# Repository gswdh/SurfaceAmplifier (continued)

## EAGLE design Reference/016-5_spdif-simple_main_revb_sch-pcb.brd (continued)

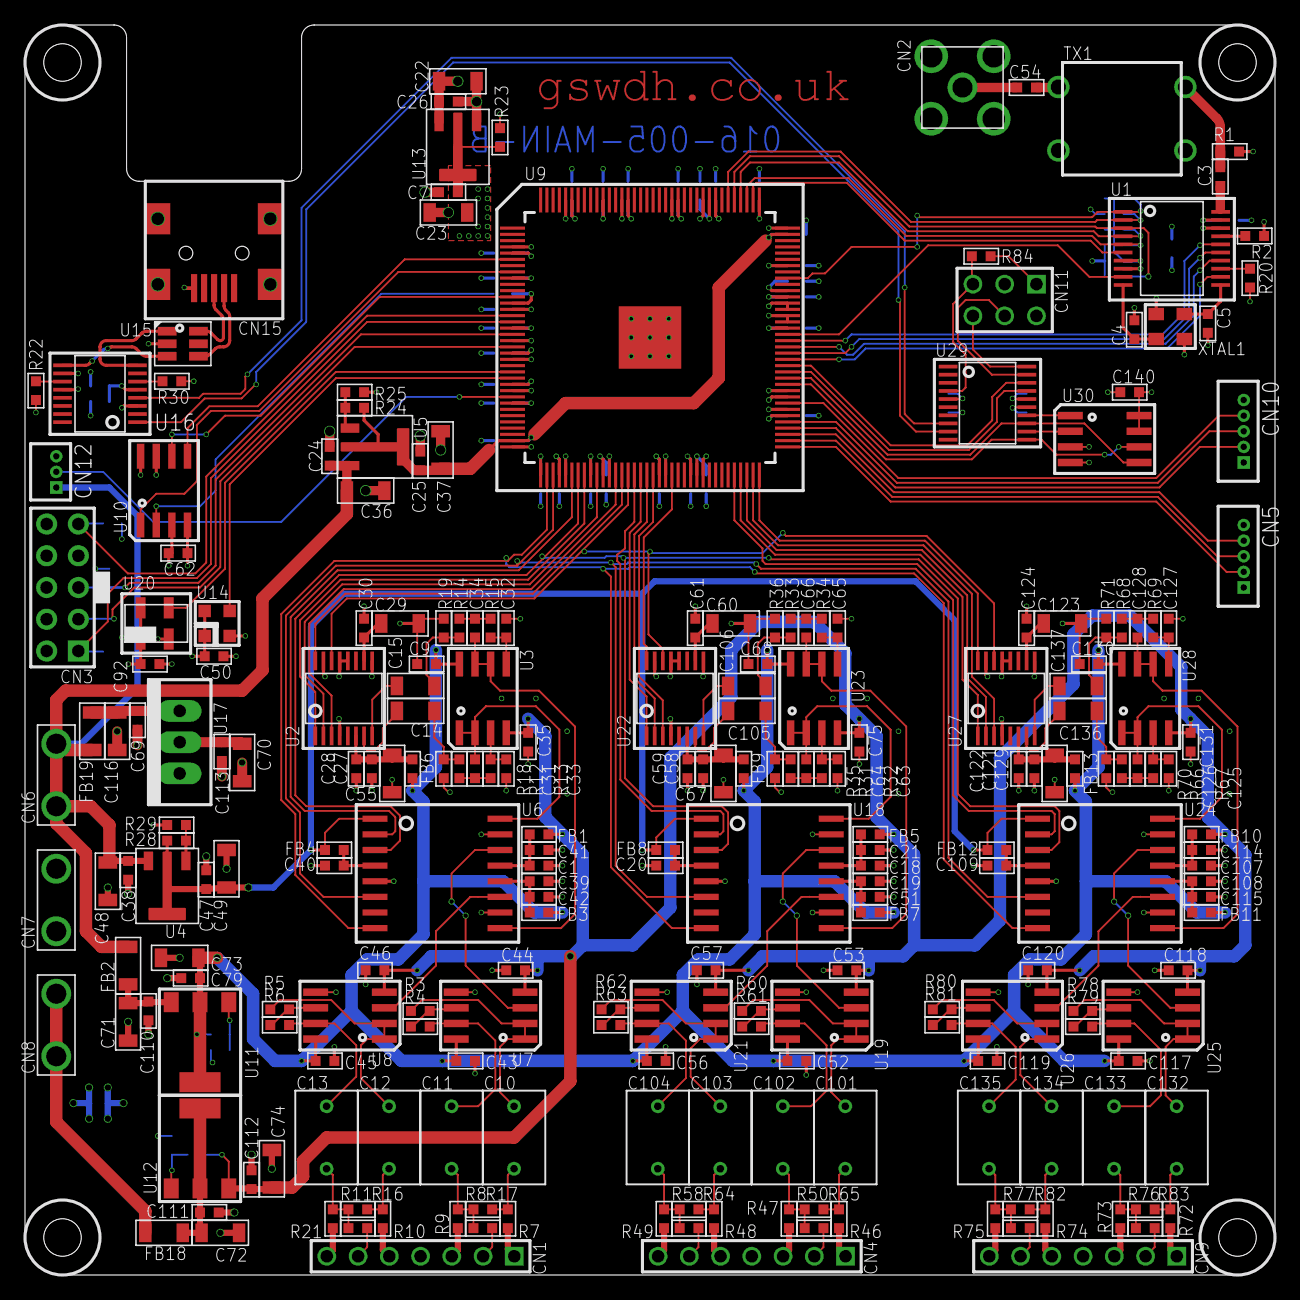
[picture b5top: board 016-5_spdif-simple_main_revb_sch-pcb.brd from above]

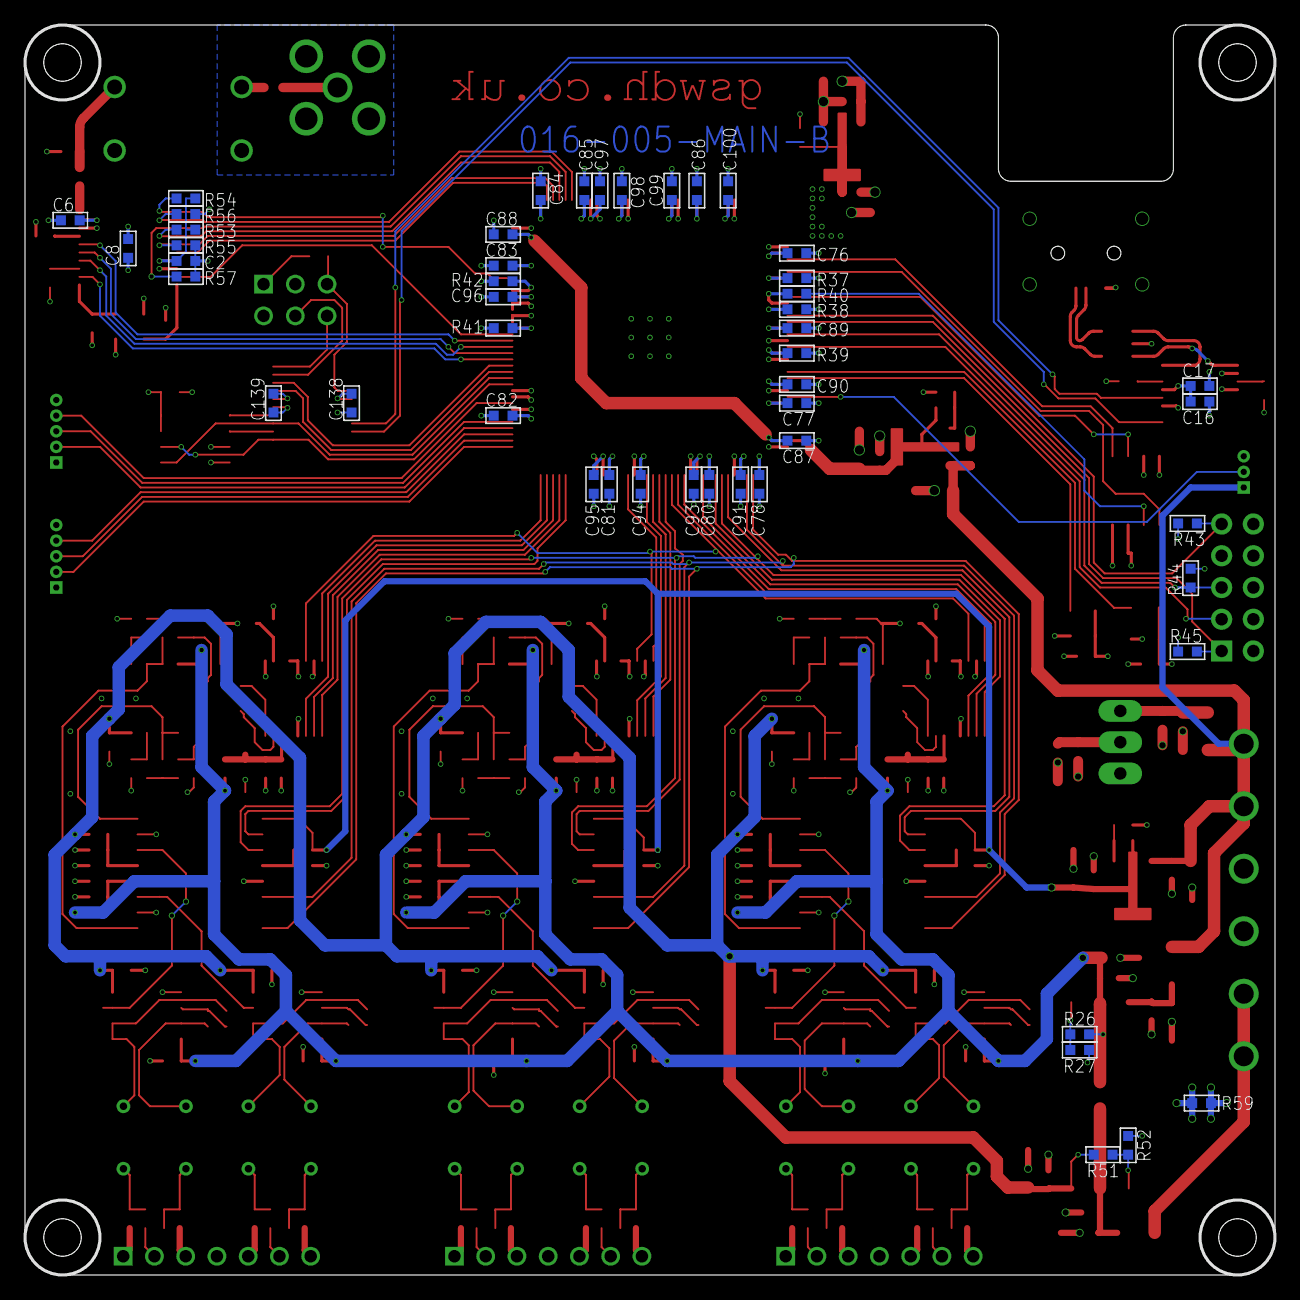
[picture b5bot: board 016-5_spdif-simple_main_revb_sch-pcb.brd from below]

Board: 4 copper layers, 100.0 x 100.0 mm, 289 parts (49 on the bottom side), 189 nets.

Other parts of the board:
U$194: GSWDH.CO.UK

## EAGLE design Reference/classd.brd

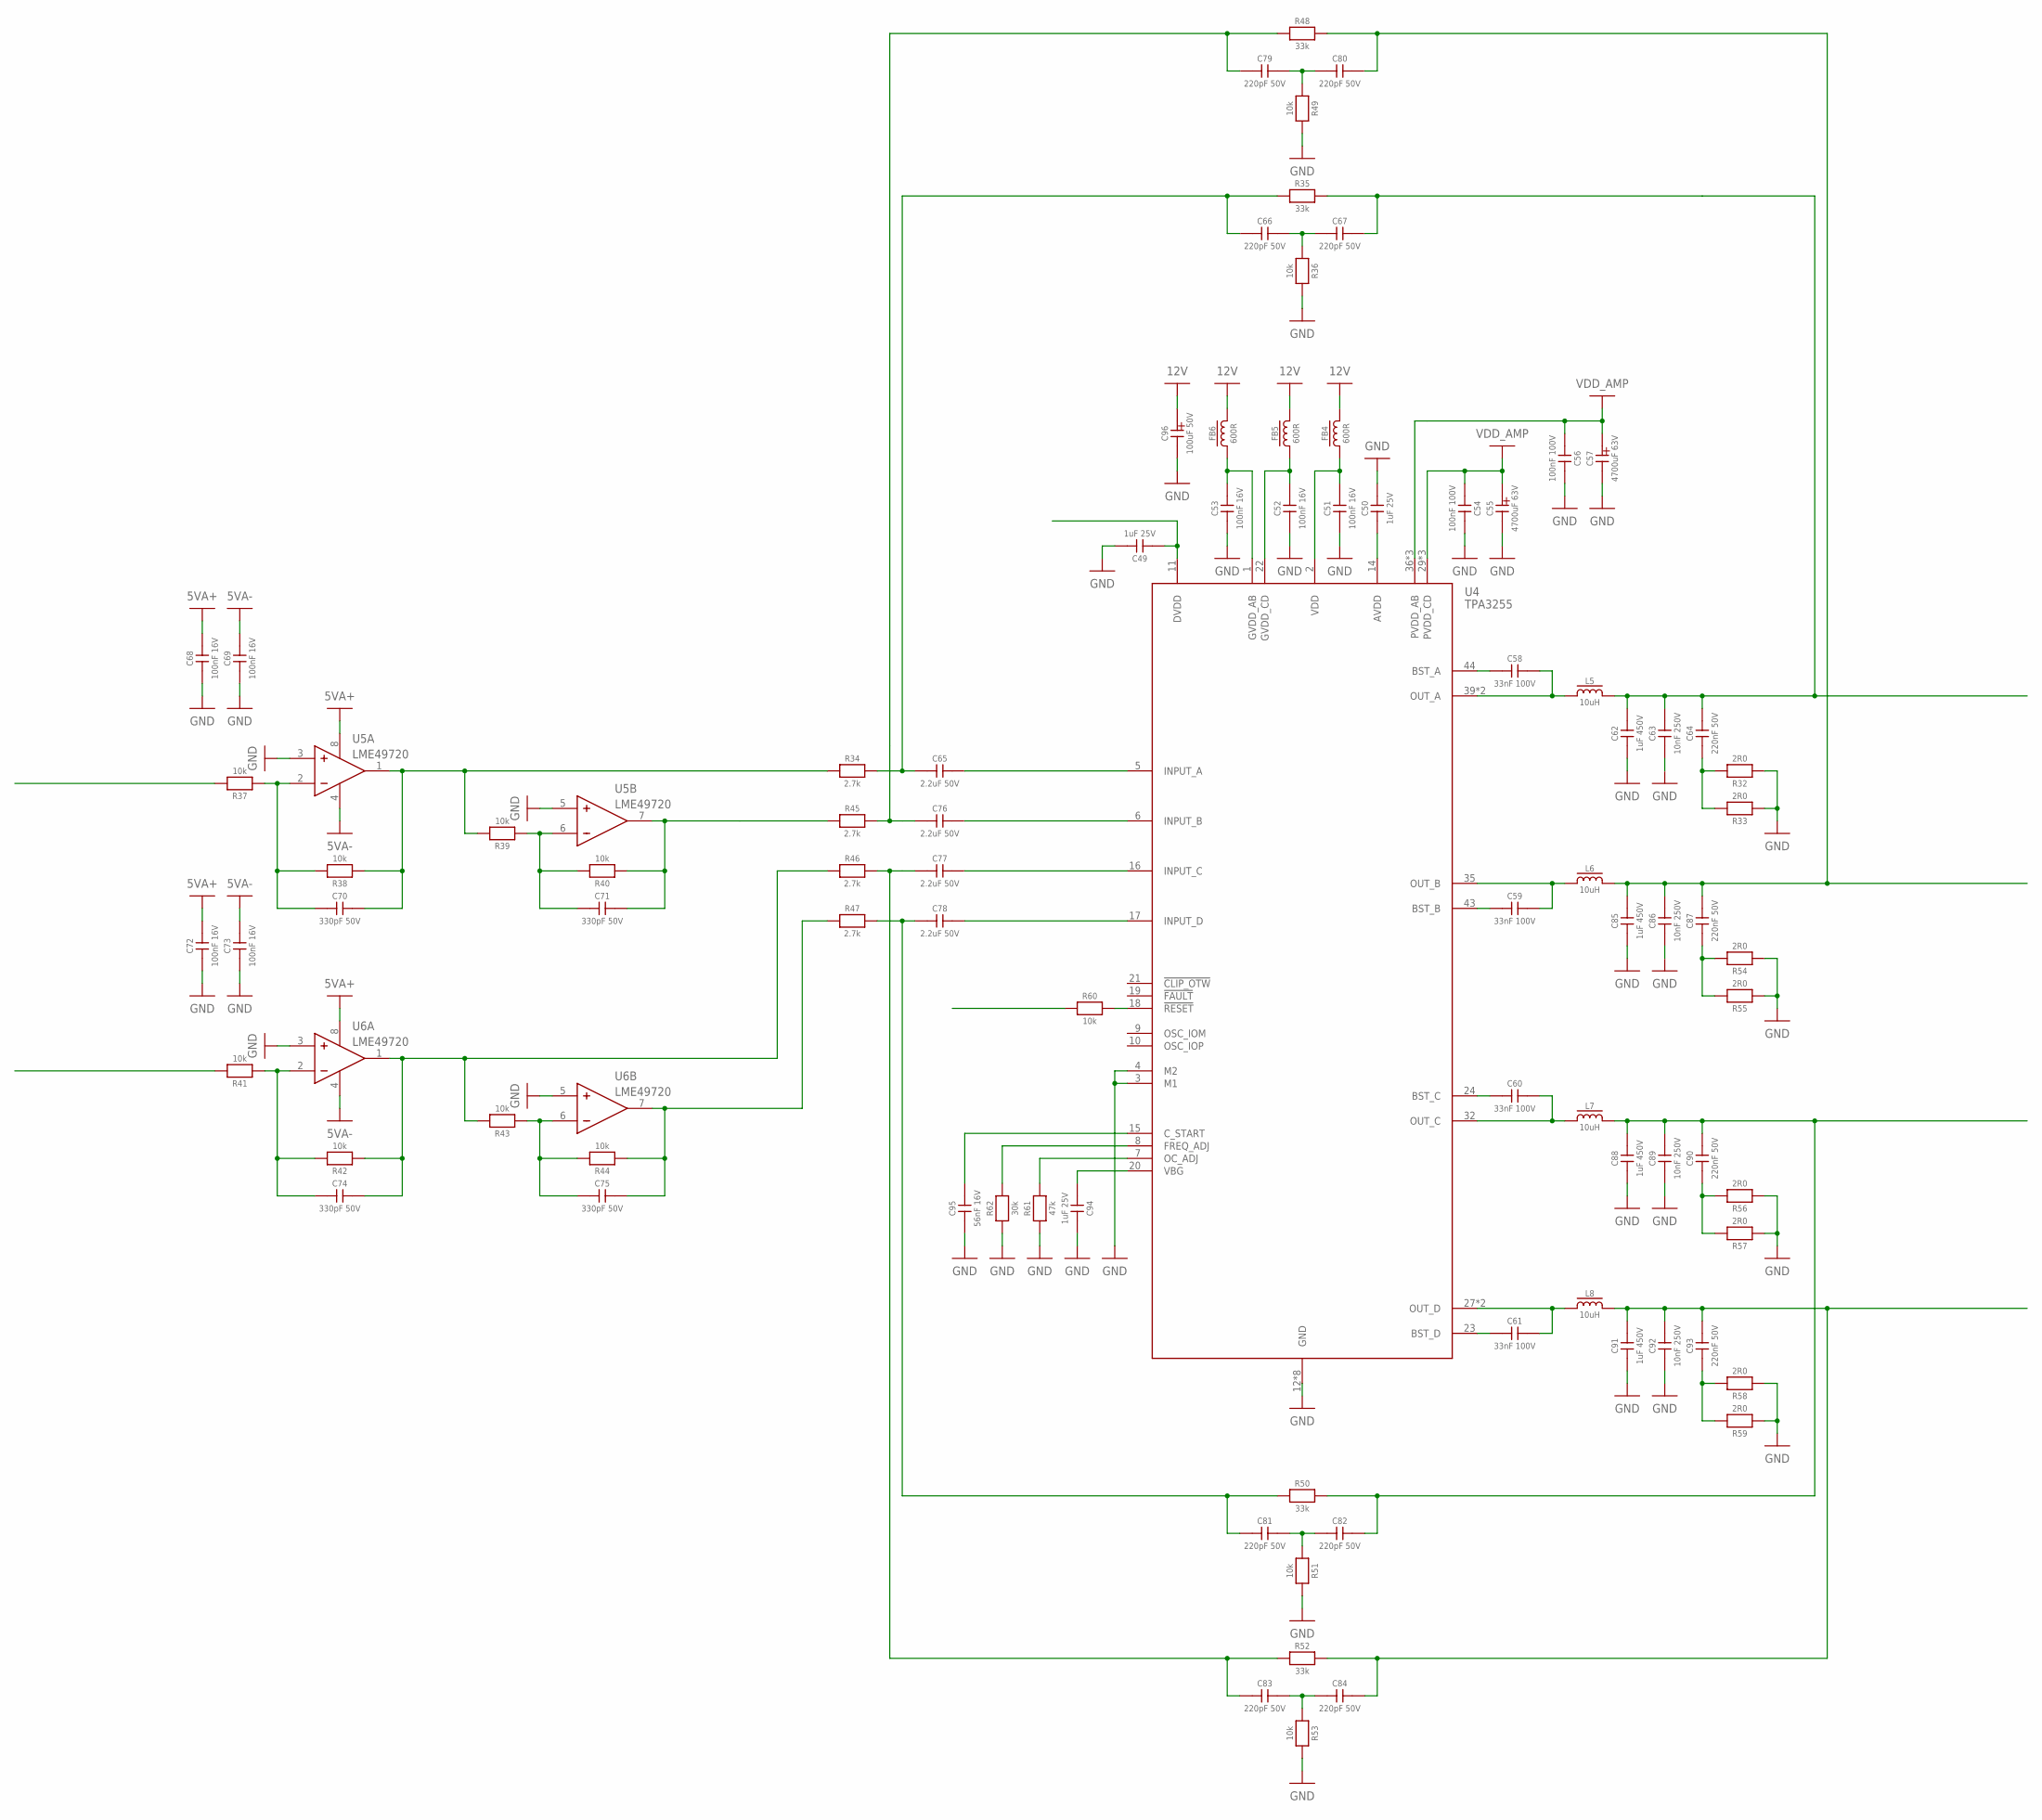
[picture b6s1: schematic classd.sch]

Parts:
C49, C50, C94: 1uF 25V; 0603
C51, C52, C53, C68, C69, C72, C73: 100nF 16V; 0603
C54, C56: 100nF 100V; 0603
C55, C57: 4700uF 63V; 30MM_RADIAL_10MM_PITCH
C58, C59, C60, C61: 33nF 100V; 0603
C62, C85, C88, C91: 1uF 450V; 7X17.5BOX
C63, C86, C89, C92: 10nF 250V; 0603
C64, C87, C90, C93: 220nF 50V; 0603
C65, C76, C77, C78: 2.2uF 50V; 5X7.2BOX
C66, C67, C79, C80, C81, C82, C83, C84: 220pF 50V; 0603
C70, C71, C74, C75: 330pF 50V; 0603
C95: 56nF 16V; 0603
C96: 100uF 50V; 8MM_RADIAL_3.5MM_PITCH
FB4, FB5, FB6: 600R; 0603
L5, L6, L7, L8: 10uH; SRP1265A
R32, R33, R54, R55, R56, R57, R58, R59: 2R0; 1206
R34, R45, R46, R47: 2.7k; 0603
R35, R48, R50, R52: 33k; 0603
R36, R37, R38, R39, R40, R41, R42, R43, R44, R49, R51, R53, R60: 10k; 0603
R61: 47k; 0603
R62: 30k; 0603
U4: TPA3255; HTSSOP44
U5, U6: LME49720; SO8

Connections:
5VA+: C68.2, C72.2, U5.8 (V+), U6.8 (V+)
5VA-: C69.2, C73.2, U5.4 (V-), U6.4 (V-)
12V: C96.P (A), FB4.2, FB5.2, FB6.2
GND: C49.2, C50.2, C51.1, C52.1, C53.1, C54.2, C55.1 (K), C56.2, C57.1 (K), C62.1, C63.1, C68.1, C69.1, C72.1, C73.1, C85.1, C86.1, C88.1, C89.1, C91.1, C92.1, C94.2, C95.1, C96.N (K), R32.1, R33.1, R36.2, R49.2, R51.2, R53.2, R54.1, R55.1, R56.1, R57.1, R58.1, R59.1, R61.1, R62.1, U4.3 (M1), U4.4 (M2), U4.12 (GND), U4.13 (GND), U4.25 (GND), U4.26 (GND), U4.33 (GND), U4.34 (GND), U4.41 (GND), U4.42 (GND), U5.3 (+), U5.5 (+), U6.3 (+), U6.5 (+)
unnamed: C50.1, U4.14 (AVDD)
unnamed: C51.2, FB4.1, U4.2 (VDD)
unnamed: C52.2, FB5.1, U4.22 (GVDD_CD)
unnamed: C53.2, FB6.1, U4.1 (GVDD_AB)
unnamed: C61.1, U4.23 (BST_D)
unnamed: C61.2, L8.1, U4.27 (OUT_D), U4.28 (OUT_D)
unnamed: C60.1, U4.24 (BST_C)
unnamed: C60.2, L7.1, U4.32 (OUT_C)
unnamed: C59.1, U4.43 (BST_B)
unnamed: C59.2, L6.1, U4.35 (OUT_B)
unnamed: C58.1, U4.44 (BST_A)
unnamed: C58.2, L5.1, U4.39 (OUT_A), U4.40 (OUT_A)
unnamed: C64.1, R32.2, R33.2
unnamed: C65.2, U4.5 (INPUT_A)
unnamed: C65.1, C66.1, R34.2, R35.1
unnamed: C62.2, C63.2, C64.2, C67.2, L5.2, R35.2
unnamed: C66.2, C67.1, R36.1
unnamed: C70.2, R34.1, R38.1, R39.2, U5.1 (OUT)
unnamed: C70.1, R37.1, R38.2, U5.2 (-)
unnamed: C71.2, R40.1, R45.1, U5.7 (OUT)
unnamed: C71.1, R39.1, R40.2, U5.6 (-)
unnamed: C74.2, R42.1, R43.2, R46.1, U6.1 (OUT)
unnamed: C74.1, R41.1, R42.2, U6.2 (-)
unnamed: C75.2, R44.1, R47.1, U6.7 (OUT)
unnamed: C75.1, R43.1, R44.2, U6.6 (-)
unnamed: C76.2, U4.6 (INPUT_B)
unnamed: C77.2, U4.16 (INPUT_C)
unnamed: C78.2, U4.17 (INPUT_D)
unnamed: C76.1, C79.1, R45.2, R48.1
unnamed: C80.2, C85.2, C86.2, C87.2, L6.2, R48.2
unnamed: C79.2, C80.1, R49.1
unnamed: C78.1, C81.1, R47.2, R50.1
unnamed: C82.2, C88.2, C89.2, C90.2, L7.2, R50.2
unnamed: C81.2, C82.1, R51.1
unnamed: C77.1, C83.1, R46.2, R52.1
unnamed: C84.2, C91.2, C92.2, C93.2, L8.2, R52.2
unnamed: C83.2, C84.1, R53.1
unnamed: C87.1, R54.2, R55.2
unnamed: C90.1, R56.2, R57.2
unnamed: C93.1, R58.2, R59.2
unnamed: R60.2, U4.18 (!RESET)
unnamed: C94.1, U4.20 (VBG)
unnamed: R61.2, U4.7 (OC_ADJ)
unnamed: R62.2, U4.8 (FREQ_ADJ)
unnamed: C95.2, U4.15 (C_START)
TPA_VDD_1: C49.1, R60.1, U4.11 (DVDD)
VDD_AMP: C54.1, C55.2 (A), C56.1, C57.2 (A), U4.29 (PVDD_CD), U4.30 (PVDD_CD), U4.31 (PVDD_CD), U4.36 (PVDD_AB), U4.37 (PVDD_AB), U4.38 (PVDD_AB)

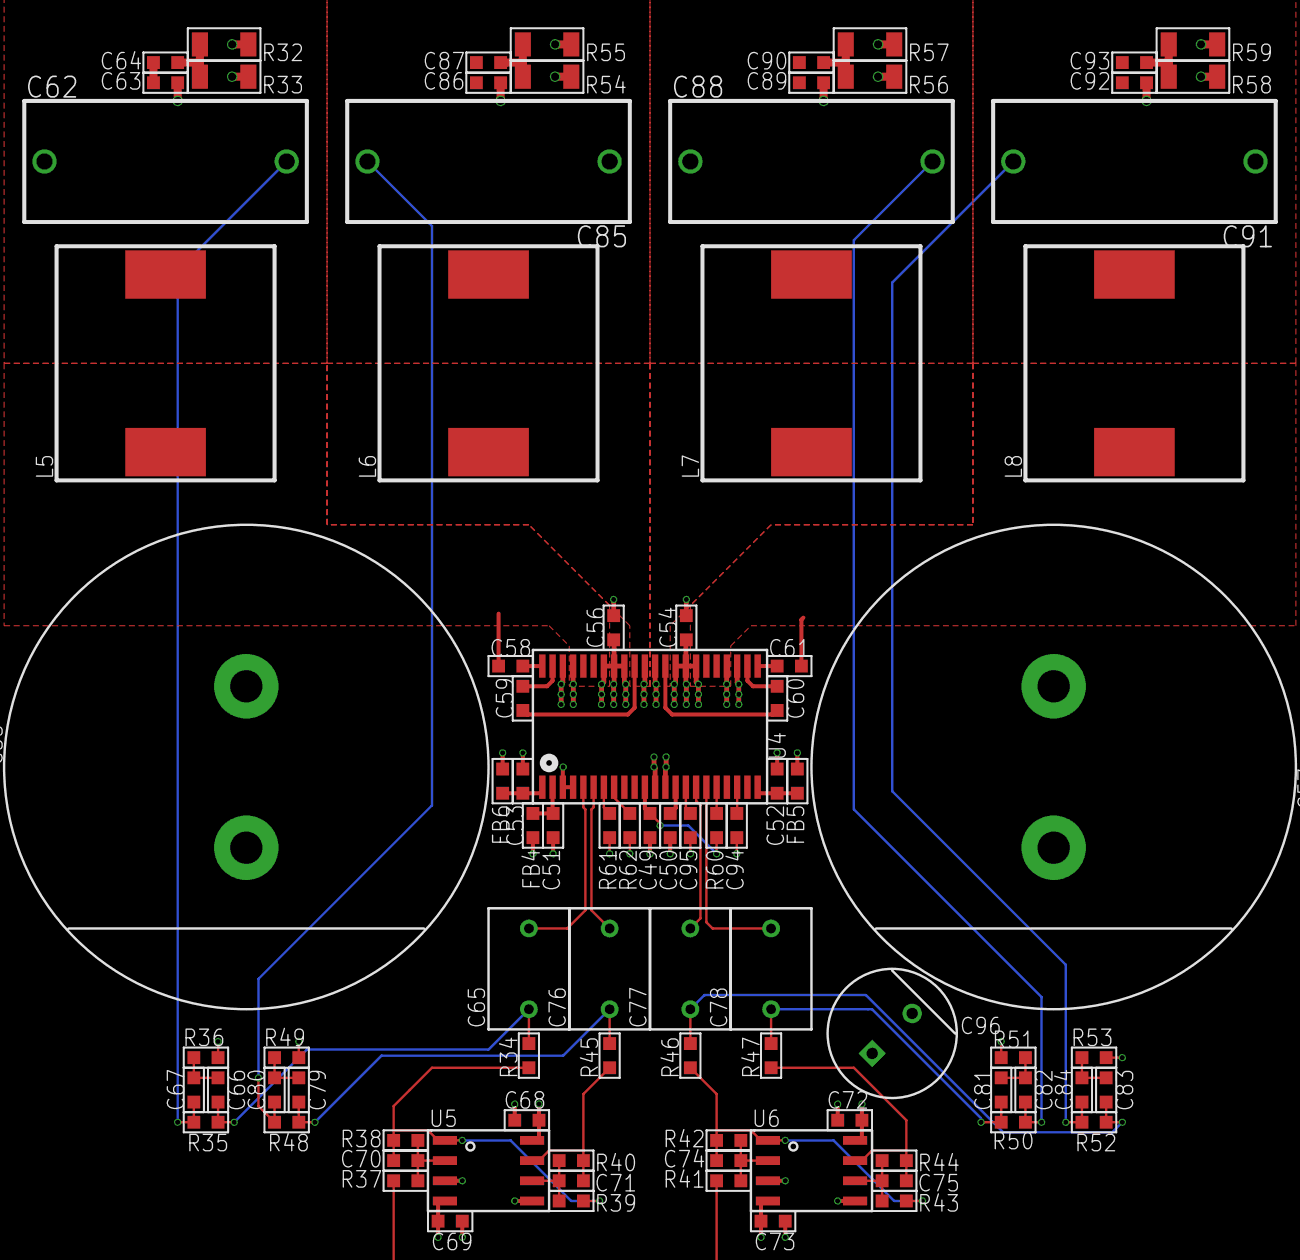
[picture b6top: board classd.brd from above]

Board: 4 copper layers, 89 parts (0 on the bottom side), 51 nets.

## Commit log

2019-12-28 PSU Schematic start
2019-12-28 Work on the PSU
2019-12-29 Ready for layout
2019-12-29 Layout nearly complete
2019-12-30 Work on the amplifier
2019-12-31 Renamed
2019-12-31 Started the DSP
2020-01-01 Work on the DSP
2020-01-01 Added FPGA
2020-01-03 USB added
2020-01-03 Additions
2020-01-14 Amplifier modules ready to be made
2020-01-14 Removed CAMOutputs
2020-01-24 Routing the DACs to the FPGA
2020-01-25 Routing the anallogue section
2020-01-25 General progress
2020-01-25 Libraies sorted
2020-01-30 DSP progress
2020-01-30 Added female USB
2020-01-31 USB hub added
2020-02-01 USB routed
2020-02-02 Working on PSUs
2020-02-03 Progress on DSP
2020-02-08 PSUs done for the FPGA
2020-02-09 Progress
2020-02-16 FPGA config needs check, full review, DRC, airwires and architecture review needed
2020-02-17 Schmit triggers done, FPGA conf done
2020-02-17 Passes DRC
2020-02-17 Analogue output connections added
2020-02-18 Connect mode button
2020-02-18 Started IO board
2021-01-21 Master reset circuitry added
2022-02-02 New concept TPA3255 amplifier
2022-02-03 new power amp and input PCBs
2022-02-07 Updated amplifier boards
2022-02-09 Improved layout of the sa_amp
2022-02-16 Pushed input board to fusion
2023-01-03 amp fixed
2025-02-15 DSP main board nearly done. All others have some changes not sure what
